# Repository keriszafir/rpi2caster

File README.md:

rpi2caster
==========

Raspberry Pi controls a Monotype composition caster.
----------------------------------------------------

Based on computer2caster by John Cornelisse Original idea described at
<http://letterpress.ch>

Typesetting and casting software for a Raspberry Pi-based computer
control attachment for Monotype composition casters.

This program suite consists of three major parts:

1.  Typesetting program for parsing UTF-8 text, calculating
    justification and coding it as a series of control codes accepted by
    the Monotype composition caster,
2.  Casting program for sending said codes to the casting machine using
    an interface with 32 pneumatic outputs, a pneumatic connection block
    attached to the caster's paper tower and a machine cycle
    sensor input. The program also allows to cast sorts, test the
    machine or set a short text on-the-fly, then cast the composed type.
3.  Inventory management program for adding, editing and deleting the
    definitions for replaceable machine components: normal wedges and
    matrix cases (diecases).

The workflow is as follows: 1. define matrix case layouts for your
matrix cases (and edit if needed), 2. define your normal wedges so that
the program knows what series in which set widths you have, 3. use a
typesetting program to generate a "ribbon" i.e. series of control codes
from a text, for a specified matrix case and normal wedge, 4. use the
casting program to test the machine/interface, perform machine
adjustments, and cast the type from ribbon you made earlier.

### Things you need to do

1.  Get a Raspberry Pi mod B+ or 2B and install Raspbian
2.  Use Raspbian jessie or stretch
3.  Make a pneumatic interface that attaches on the Monotype's paper
    tower - or have it made by someone with a CNC mill, 3D printer etc.
    This is the hardest part. The pneumatic interface must be very
    precisely done, so that no air leaks out.
4.  Get 31 three-way solenoid valves on valve islands. 12 or 24V DC.
    IMPORTANT: Some valves require minimum air pressure of 2...2.5bar.
    Since the Monotype caster uses 1bar, the pressure differential
    across the valve will be too low and the valve won't open. We need
    the 0bar minimum pressure variety, even though they may take more
    electrical power. A great candidate is the MATRIX BX758-8E1C3-24.
    The valve block is very compact and looks a bit like a
    stepper motor. It features up to 8 valves in a 55x55mm enclosure,
    with 12V DC or 24V DC controls and minimal pressure of 0 bar (this
    is important - we'll be using just 1bar!) The cost is about 200 Euro
    per piece (we need a set of 4). Another good candidates are e.g. two
    Festo CPV10-GE-MP-8 islands with 8 x "C" valve (i.e. dual 3/2) and
    separate connections for pilot supply.
5.  Make a RPi to 32 open collector output interface (the Raspberry's
    native GPIO pins cannot drive 24V loads, and there's not enough
    of them). Check out
    <https://github.com/elegantandrogyne/rpi2caster-doc-hardware> for
    the documentation (electrical in Eagle, PDF and Gerber, mechanical
    in CorelDraw) of my interface.
6.  Resolve the dependencies as described further.
7.  Install this software on your RPi.

### System config

The most common distro is Raspbian and we'll use jessie or newer. If you
need GUI (HDMI connection from Raspberry to monitor/TV, local console),
choose the standard image; otherwise (for headless setup) use minimal.
Assuming that you know your way around the Raspberry, SSH into it, set
it up (you must enable I2C), choose locale, change password, update the
system etc.

-   Network setup - I recommend configuring your router to offer the
    Raspberry a static DHCP lease based on the MAC address. If that's
    not possible (e.g. you don't have admin access to the router), use
    static IP address or scan the network for a host with the RPi's MAC
    address after each boot.
-   User & security config advice:
    1.  Create user accounts and disable no-password sudoing for "pi" by
        commenting out the respective line in /etc/sudoers.
    2.  Add new users to groups user "pi" belongs to. For security
        reasons, you may want to remove "pi" from the "sudo" and
        "adm" groups.
    3.  Since you'll log on the machine via SSH, you can use a RSA key
        authentication instead of entering a password on each logon.
        Either use a "ssh-copy-id \[target-username@\]target-host"
        command or create a \~/.ssh/authorized\_keys file on the
        Raspberry and paste your id\_rsa.pub contents there. Then you
        can just ssh by typing "ssh \[username@\]monotype" or via PuTTY.
-   Various improvements
    1.  You can enable GUI access by VNC. Install tightvncserver. Edit
        /etc/lightdm/lightdm.conf and uncomment the lines in
        VNC section. Change the port, geometry etc. if you wish. You
        don't have to create any init scripts; lightdm will already take
        care of running the VNC server. Just run "vncviewer \[hostname
        or IP addr\]:\[port\]" client-side and you'll get a lightdm
        login screen. Sign in to your account.
    2.  Using a web-based SSH client might be a good idea. I've used
        shellinabox with great results. This way, you won't have to
        install any additional software, esp. if you're using M\$
        Windows (otherwise, you'll need PuTTY or other SSH client).
-   Get rid of unneeded stuff! The original Raspbian distro has some
    unneeded software installed by default. We can get rid of it by
    using "sudo aptitude purge...":
    1.  wolfram-engine - removing it will clean somewhere around
        450MB (!)
    2.  X, LXDE etc. unless you want to VNC into the machine or set up a
        local console with GUI
    3.  anything related to Scratch
    4.  Minecraft or any other games, LibreOffice etc., they're huge
        diskspace hogs, not really needed

### Dependencies

Some of the dependencies will be marked as "(repo)". This means that you
can install them from Raspbian repository using apt or aptitude.

1.  python3 - doesn't come with minimal Jessie, and rpi2caster is
    written in python3 only (it's relatively new and there's no need for
    backwards compatibility)
2.  python3-pip - for installing python3 packages (install it with apt
    or aptitude; python3 will be installed automatically)
3.  wiringpi2-python - Python bindings for wiringpi2. You can install it
    with pip3: `sudo pip3 install wiringpi2` - necessary for program to
    work!

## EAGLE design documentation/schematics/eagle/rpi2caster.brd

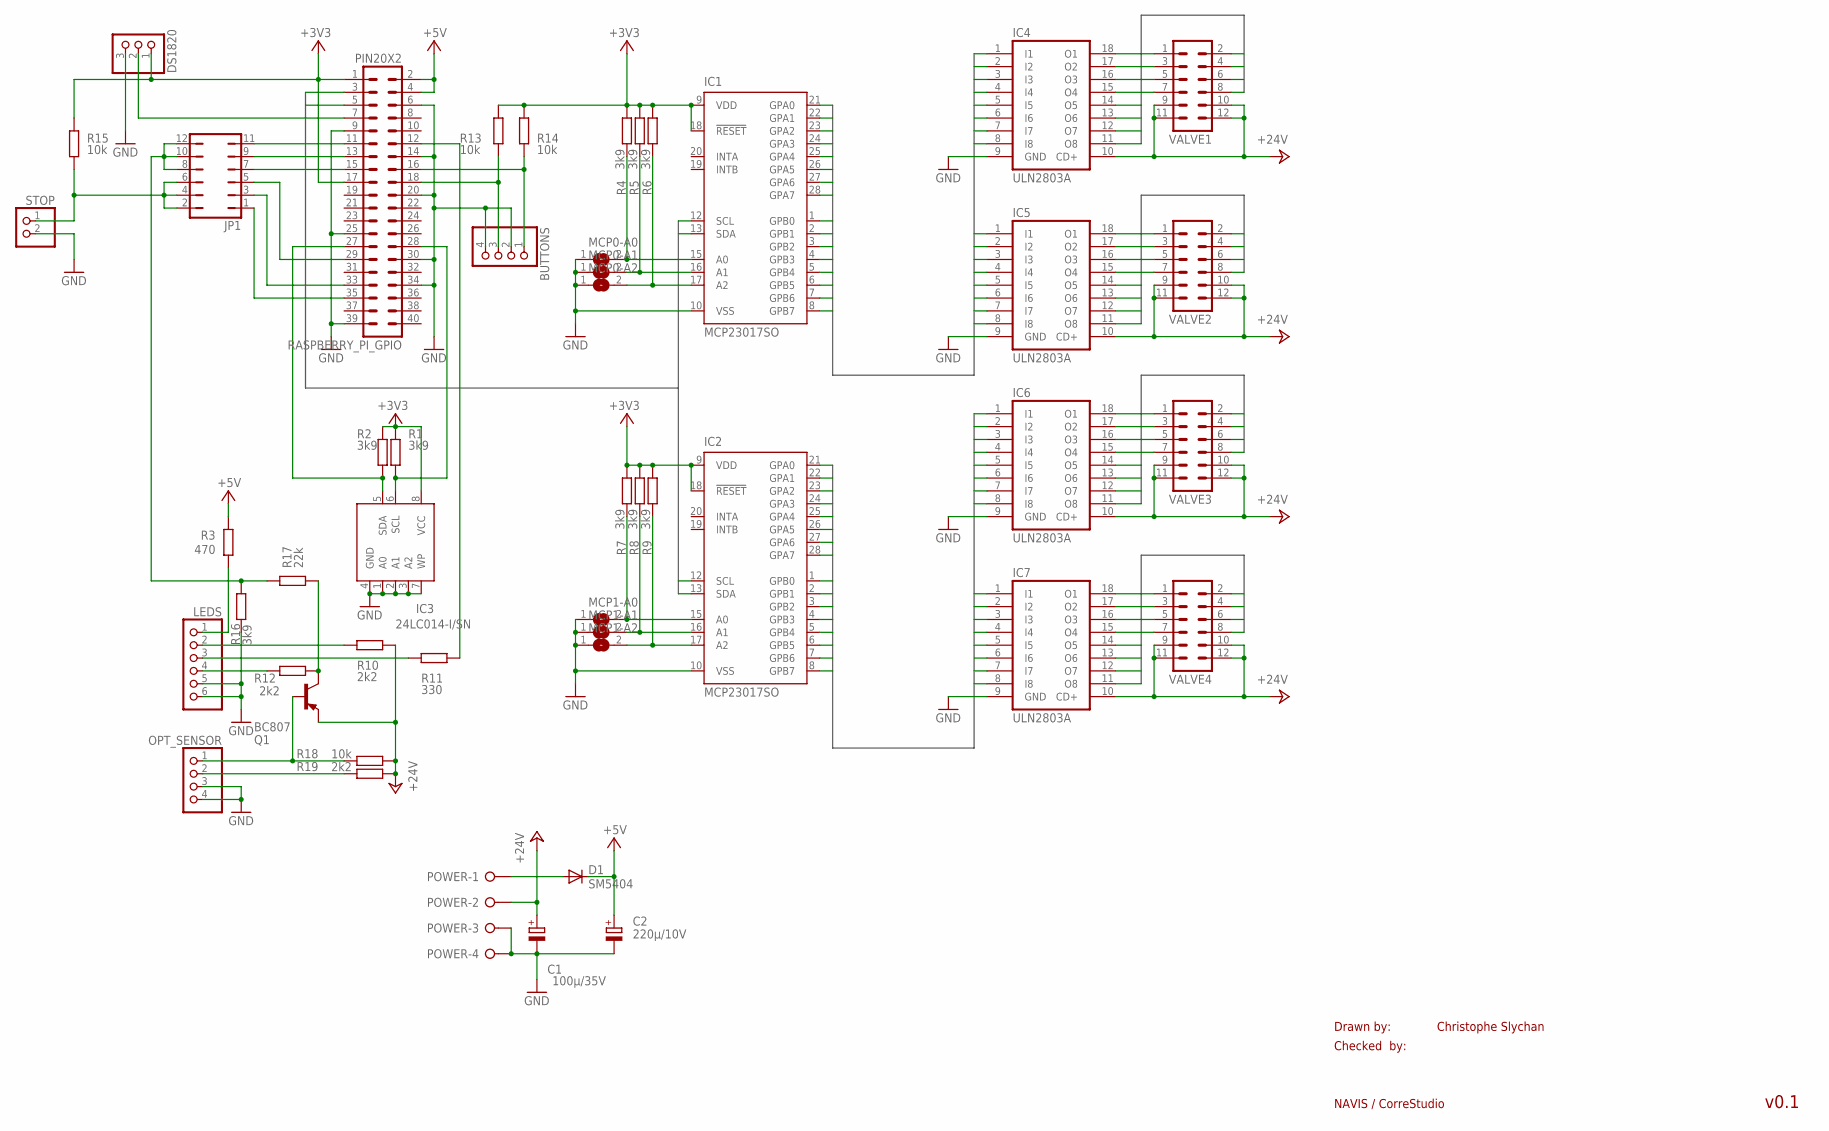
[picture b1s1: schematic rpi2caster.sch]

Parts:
BUTTONS: PINHD-1X4; 1X04
C1: 100µ/35V; E5-6
C2: 220µ/10V; E2,5-7
D1: SM5404; MELF-MLL41
DS1820: PINHD-1X3; 1X03
IC1, IC2: MCP23017SO; SO28W
IC3: 24LC014-I/SN; SOIC8
IC4, IC5, IC6, IC7: ULN2803A; SO18W
JP1: JP6Q
LEDS: PINHD-1X6; 1X06
MCP0-A0, MCP0-A1, MCP0-A2, MCP1-A0, MCP1-A1, MCP1-A2: SJ
OPT_SENSOR: PINHD-1X4; 1X04
POWER: W237-04P; W237-4P
Q1: BC807; SOT23-BEC
R1, R2, R4, R5, R6, R7, R8, R9, R16: 3k9; M0805; TOLERANCE 5%
R3: 470; M0805; TOLERANCE 5%
R10, R12, R19: 2k2; M0805; TOLERANCE 5%
R11: 330; M0805; TOLERANCE 5%
R13, R14, R15, R18: 10k; M0805; TOLERANCE 5%
R17: 22k; M0805; TOLERANCE 5%
RASPBERRY_PI_GPIO: PIN20X2; PIN_20X2
STOP: PINHD-1X2; 1X02
VALVE1, VALVE2, VALVE3, VALVE4: MA06-2

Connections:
+3V3: DS1820.1, IC1.9 (VDD), IC1.18 (!RESET), IC2.9 (VDD), IC2.18 (!RESET), IC3.8 (VCC), R1.1, R2.1, R4.2, R5.2, R6.2, R7.2, R8.2, R9.2, R13.2, R14.2, R15.2, RASPBERRY_PI_GPIO.1, RASPBERRY_PI_GPIO.17
+5V: C2.+, D1.C, R3.2, RASPBERRY_PI_GPIO.2, RASPBERRY_PI_GPIO.4
+24V: C1.+, IC4.10 (CD+), IC5.10 (CD+), IC6.10 (CD+), IC7.10 (CD+), POWER.2, Q1.E, R10.2, R18.1, R19.1, VALVE1.9, VALVE1.10, VALVE1.11, VALVE1.12, VALVE2.9, VALVE2.10, VALVE2.11, VALVE2.12, VALVE3.9, VALVE3.10, VALVE3.11, VALVE3.12, VALVE4.9, VALVE4.10, VALVE4.11, VALVE4.12
GND: BUTTONS.2, BUTTONS.4, C1.-, C2.-, DS1820.3, IC1.10 (VSS), IC2.10 (VSS), IC3.1 (A0), IC3.2 (A1), IC3.3 (A2), IC3.4 (GND), IC3.7 (WP), IC4.9 (GND), IC5.9 (GND), IC6.9 (GND), IC7.9 (GND), LEDS.5, LEDS.6, MCP0-A0.1, MCP0-A1.1, MCP0-A2.1, MCP1-A0.1, MCP1-A1.1, MCP1-A2.1, OPT_SENSOR.3, OPT_SENSOR.4, POWER.3, POWER.4, R16.1, RASPBERRY_PI_GPIO.6, RASPBERRY_PI_GPIO.9, RASPBERRY_PI_GPIO.14, RASPBERRY_PI_GPIO.20, RASPBERRY_PI_GPIO.25, RASPBERRY_PI_GPIO.30, RASPBERRY_PI_GPIO.34, RASPBERRY_PI_GPIO.39, STOP.2
I2C0: IC1.13 (SDA), IC2.13 (SDA), RASPBERRY_PI_GPIO.3
I2C1: IC1.12 (SCL), IC2.12 (SCL), RASPBERRY_PI_GPIO.5
MCP0_OUT0: IC1.21 (GPA0), IC4.8 (I8)
MCP0_OUT1: IC1.22 (GPA1), IC4.7 (I7)
MCP0_OUT2: IC1.23 (GPA2), IC4.6 (I6)
MCP0_OUT3: IC1.24 (GPA3), IC4.5 (I5)
MCP0_OUT4: IC1.25 (GPA4), IC4.4 (I4)
MCP0_OUT5: IC1.26 (GPA5), IC4.3 (I3)
MCP0_OUT6: IC1.27 (GPA6), IC4.2 (I2)
MCP0_OUT7: IC1.28 (GPA7), IC4.1 (I1)
MCP0_OUT8: IC1.1 (GPB0), IC5.8 (I8)
MCP0_OUT9: IC1.2 (GPB1), IC5.7 (I7)
MCP0_OUT10: IC1.3 (GPB2), IC5.6 (I6)
MCP0_OUT11: IC1.4 (GPB3), IC5.5 (I5)
MCP0_OUT12: IC1.5 (GPB4), IC5.4 (I4)
MCP0_OUT13: IC1.6 (GPB5), IC5.3 (I3)
MCP0_OUT14: IC1.7 (GPB6), IC5.2 (I2)
MCP0_OUT15: IC1.8 (GPB7), IC5.1 (I1)
MCP1_OUT0: IC2.21 (GPA0), IC6.8 (I8)
MCP1_OUT1: IC2.22 (GPA1), IC6.7 (I7)
MCP1_OUT2: IC2.23 (GPA2), IC6.6 (I6)
MCP1_OUT3: IC2.24 (GPA3), IC6.5 (I5)
MCP1_OUT4: IC2.25 (GPA4), IC6.4 (I4)
MCP1_OUT5: IC2.26 (GPA5), IC6.3 (I3)
MCP1_OUT6: IC2.27 (GPA6), IC6.2 (I2)
MCP1_OUT7: IC2.28 (GPA7), IC6.1 (I1)
MCP1_OUT8: IC2.1 (GPB0), IC7.8 (I8)
MCP1_OUT9: IC2.2 (GPB1), IC7.7 (I7)
MCP1_OUT10: IC2.3 (GPB2), IC7.6 (I6)
MCP1_OUT11: IC2.4 (GPB3), IC7.5 (I5)
MCP1_OUT12: IC2.5 (GPB4), IC7.4 (I4)
MCP1_OUT13: IC2.6 (GPB5), IC7.3 (I3)
MCP1_OUT14: IC2.7 (GPB6), IC7.2 (I2)
MCP1_OUT15: IC2.8 (GPB7), IC7.1 (I1)
unnamed: LEDS.1, R3.1
unnamed: IC3.5 (SDA), R2.2, RASPBERRY_PI_GPIO.27
unnamed: IC3.6 (SCL), R1.2, RASPBERRY_PI_GPIO.28
unnamed: OPT_SENSOR.2, R19.2
unnamed: DS1820.2, RASPBERRY_PI_GPIO.7
unnamed: IC1.15 (A0), MCP0-A0.2, R4.1
unnamed: IC1.16 (A1), MCP0-A1.2, R5.1
unnamed: IC1.17 (A2), MCP0-A2.2, R6.1
unnamed: IC2.15 (A0), MCP1-A0.2, R7.1
unnamed: IC2.16 (A1), MCP1-A1.2, R8.1
unnamed: IC2.17 (A2), MCP1-A2.2, R9.1
unnamed: LEDS.2, R10.1
unnamed: LEDS.3, R11.1
unnamed: LEDS.4, R12.1
unnamed: JP1.11, RASPBERRY_PI_GPIO.11
unnamed: JP1.9, RASPBERRY_PI_GPIO.13
unnamed: R11.2, RASPBERRY_PI_GPIO.12
unnamed: BUTTONS.1, R14.1, RASPBERRY_PI_GPIO.16
unnamed: BUTTONS.3, R13.1, RASPBERRY_PI_GPIO.18
unnamed: JP1.2, JP1.4, JP1.6, R15.1, STOP.1
unnamed: JP1.8, JP1.10, JP1.12, R16.2, R17.2
unnamed: OPT_SENSOR.1, Q1.B, R18.2
unnamed: Q1.C, R12.2, R17.1
unnamed: JP1.7, RASPBERRY_PI_GPIO.15
unnamed: JP1.5, RASPBERRY_PI_GPIO.29
unnamed: JP1.3, RASPBERRY_PI_GPIO.33
unnamed: JP1.1, RASPBERRY_PI_GPIO.35
unnamed: D1.A, POWER.1
VALVE1_1: IC4.11 (O8), VALVE1.1
VALVE1_2: IC4.12 (O7), VALVE1.2
VALVE1_3: IC4.13 (O6), VALVE1.3
VALVE1_4: IC4.14 (O5), VALVE1.4
VALVE1_5: IC4.15 (O4), VALVE1.5
VALVE1_6: IC4.16 (O3), VALVE1.6
VALVE1_7: IC4.17 (O2), VALVE1.7
VALVE1_8: IC4.18 (O1), VALVE1.8
VALVE2_1: IC5.18 (O1), VALVE2.1
VALVE2_2: IC5.17 (O2), VALVE2.2
VALVE2_3: IC5.16 (O3), VALVE2.3
VALVE2_4: IC5.15 (O4), VALVE2.4
VALVE2_5: IC5.14 (O5), VALVE2.5
VALVE2_6: IC5.13 (O6), VALVE2.6
VALVE2_7: IC5.12 (O7), VALVE2.7
VALVE2_8: IC5.11 (O8), VALVE2.8
VALVE3_1: IC6.18 (O1), VALVE3.1
VALVE3_2: IC6.17 (O2), VALVE3.2
VALVE3_3: IC6.16 (O3), VALVE3.3
VALVE3_4: IC6.15 (O4), VALVE3.4
VALVE3_5: IC6.14 (O5), VALVE3.5
VALVE3_6: IC6.13 (O6), VALVE3.6
VALVE3_7: IC6.12 (O7), VALVE3.7
VALVE3_8: IC6.11 (O8), VALVE3.8
VALVE4_1: IC7.11 (O8), VALVE4.1
VALVE4_2: IC7.12 (O7), VALVE4.2
VALVE4_3: IC7.13 (O6), VALVE4.3
VALVE4_4: IC7.14 (O5), VALVE4.4
VALVE4_5: IC7.15 (O4), VALVE4.5
VALVE4_6: IC7.16 (O3), VALVE4.6
VALVE4_7: IC7.17 (O2), VALVE4.7
VALVE4_8: IC7.18 (O1), VALVE4.8

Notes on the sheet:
Drawn by:
Checked by:
NAVIS / CorreStudio
Christophe Slychan
v0.1

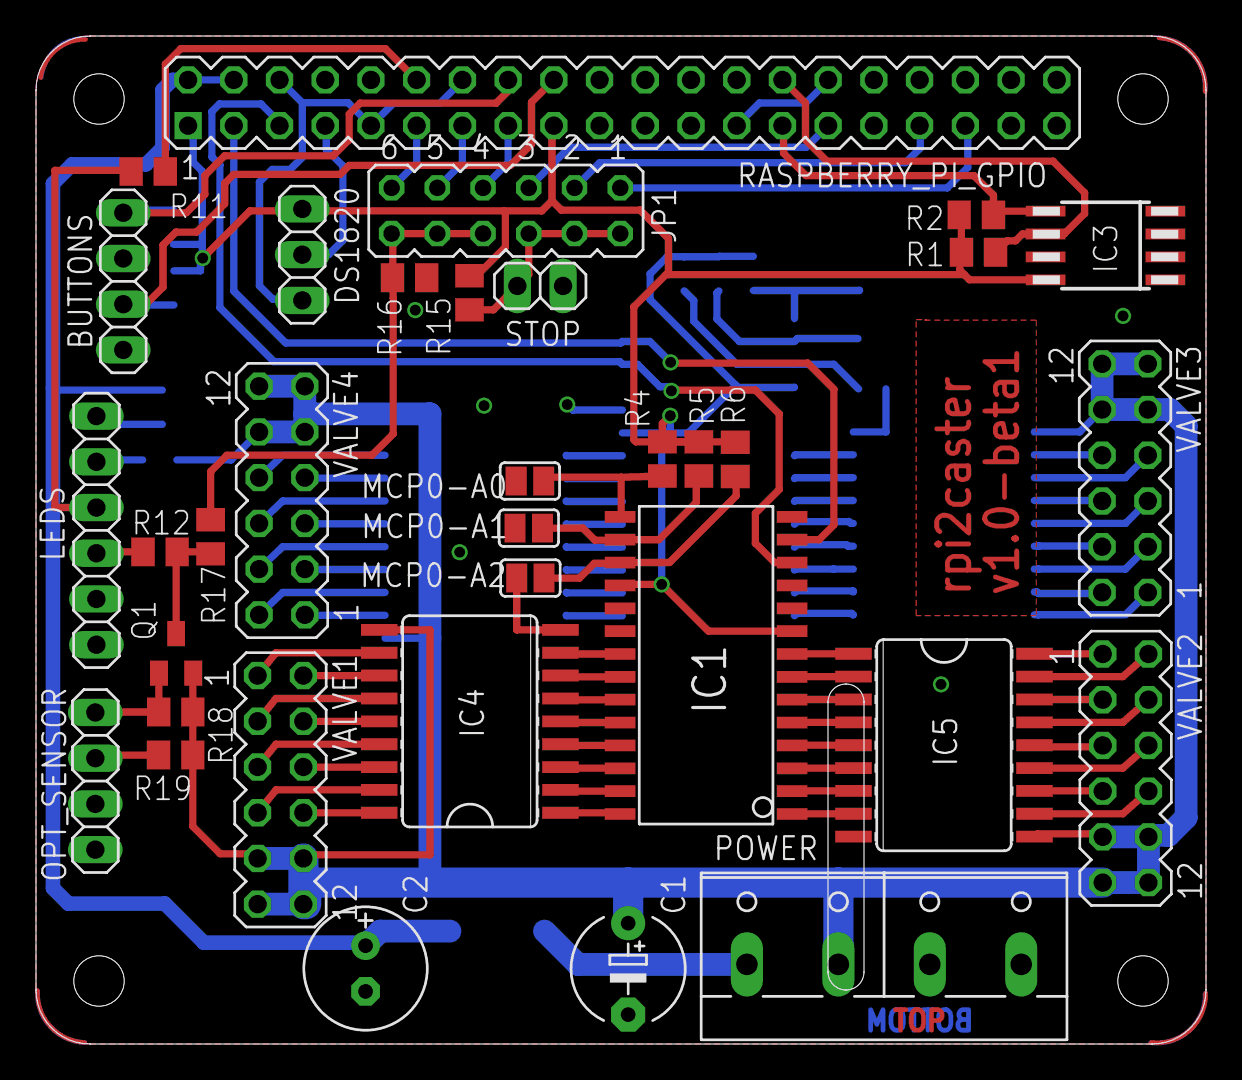
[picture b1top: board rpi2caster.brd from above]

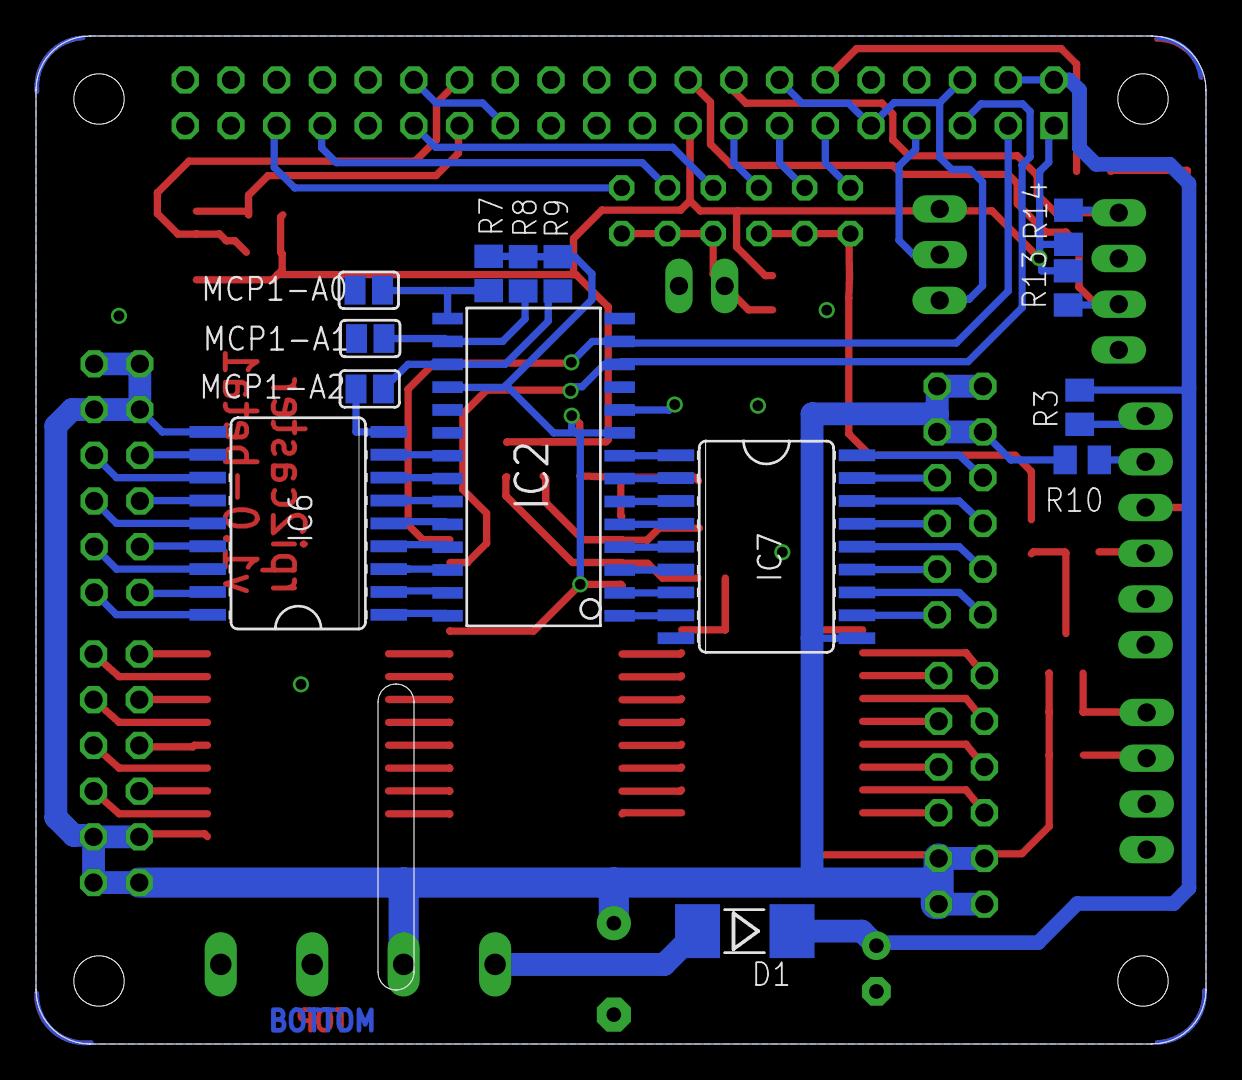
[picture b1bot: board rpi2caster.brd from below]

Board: 2 copper layers, 65.0 x 56.0 mm, 48 parts (14 on the bottom side), 98 nets.

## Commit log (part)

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2016-02-15 Ship the fix to PyPI
2016-02-15 Start integrating workflows in casting and perforation...
2016-02-16 Configuration parsing bugfix
2016-02-17 Modular casting rework in progress
2016-02-17 Sorts casting debug
2016-02-18 Work on casting function
2016-02-18 Fix temporary ribbon setting being not so temporary after all...
2016-02-18 More work on stats... and ribbon relations as well
2016-02-18 Better ribbon, diecase, wedge and stats updating, using property decorators
2016-02-19 Pump status update and restart logic rework in progress
2016-02-19 Debug wrong configuration
2016-02-19 Bugfix: hardware instantiation where unneeded
2016-02-19 Sensor and output release (instance deletion) before casting
2016-02-19 Add a hack for not reusing pin numbers with wiringPi
2016-02-19 Fix import loop
2016-02-19 Fix prompt in ui.confirm
2016-02-19 Rework of menu system; add direct casting mode with no menu; various bugfixes
2016-02-20 Various fixes and reworks
2016-02-21 Simplify the wedge, diecase, ribbon and work choice workflow
2016-02-22 Various fixes and refactors
2016-02-22 Work on statistics getting and setting
2016-02-22 Linting and regression fixes
2016-02-23 Add line skipping in casting mode
2016-02-24 More stat tweaks
2016-02-25 Space and sorts casting; diecase calibration; various fixes and reworks
2016-02-26 Support for HMN and unit-shift during casting
2016-02-26 Add comments in space casting
2016-02-27 Ditch the unit shift; ditch the works; add fount schemes instead (in ORM layer for now)
2016-02-27 Add metadata when exporting ribbon files
2016-02-27 Move processing O15 and row 16 to a decorator over casting.process
2016-03-01 Rewrite and refactor the stats logic - still on the hunt for some bugs
2016-03-02 Refactor stats.code_parameters, fix bug in monotype.adjust_signals that would turn all on in testing mode
2016-03-02 Further tweaking, testing and debugging in stats section
2016-03-02 Push to PyPI
2016-03-02 Casting workflow fixes
2016-03-04 Matrix auto-selection for casting typecases and typesetting; minor reworks on casting workflow; work on typesetting program
2016-03-06 Further work on diecase layout editing
2016-03-07 Better line length setting
2016-03-07 Casting sorts with no diecase selected: char and style(s) no longer needed
2016-03-08 Change casting sorts, add draw rod calibration
2016-03-08 Disable the ad-hoc typesetting - undergoing rework
2016-03-09 Work on typecase casting functions
2016-03-10 Add hundreds of new wedge definitions
2016-03-12 Rework of ribbon model
2016-03-13 Add diecase and wedge selection by command line parameter; rework wedge choice - display old style names, parse new style names only (KISS!)
2016-03-14 More usability fixes
2016-03-14 More powerful matrix lookup in diecase
2016-03-14 Simplify edit matrix, rearrange Matrix class to put attributes at the end
2016-03-15 Rework of sorts casting; usability fixes for diagnostics - default repeat
2016-03-15 Better batch casting - fill lines to desired length;
2016-03-16 Cast sorts/spaces/typecases rework to build upon cast_batch; UI input prompts rework; raise ReturnToMenu on blank filenames
2016-03-16 Simplify casting - no more lines of quads and preheat mould. This will be specified upstream.
2016-03-16 Fix for space styles in matrix case layout editor
2016-03-16 Bugfix in diecase selection
2016-03-16 Mould prehead quad quantity fix
2016-03-17 Optimize the generators in ribbon parser in stats module; work on new typecase casting based on letter frequencies
2016-03-18 Further menu tweaks
2016-03-18 Remove mention of deprecated inventory management mode
2016-03-19 Remove unneeded defaults; set wedge parser-wise Add matrix units re-calculation for alternative wedge
2016-03-20 Alternative wedge getter bugfix
2016-03-26 Class-based language selection and typecase casting
2016-03-26 Disable line skipping for 1-line cast jobs
2016-03-26 Space casting: move to point calculations and refactor
2016-03-26 Minor fixes
2016-03-26 Do not display units on manual matrix choice if multiple matches
2016-03-26 Move text_ui.enter_line_length to typesetting_funcs.enter_measure; change output to points; refactor ts_f a bit
2016-03-26 Add unit values for S791 wedge
2016-03-26 Boost point calculation precision; make wedge_positions an attribute
2016-03-26 Minor fix in enter_measure parameter
2016-03-27 Style and width limits fix for spaces
2016-03-27 Move to string-based coordinate setting for Matrix objects
2016-03-27 Data model change (BREAKS COMPATIBILITY): diecase layout: styles -> string; column string, row int -> coordinates string
2016-04-01 Rebuild of matrix backend; work on galley building; performance testing and debugging; typecase casting functionality
2016-04-01 Mode cleanup on exception
2016-04-03 Use explicit "from module import Class"; refactor styles
2016-04-03 Line class for typesetting
2016-04-03 Casting workflow refactor, fixes in diagnostics routines
2016-04-03 Readability tweaks
2016-04-03 Add testing function for HMN, KMN and unit-shift
2016-04-03 Start new typesetting utility
2016-04-05 Typesetting session
2016-05-01 Vast remodelling; user-based configuration and database; length class etc.
2016-05-01 Final touches before release
2016-05-03 Bugfix in mat boolean and galley builder
2016-05-05 Bump version
2016-05-07 Add backend for old parallel interface from Symbiosys; minor changes follow; rework singleton
2016-05-07 UI tweaks
2016-05-07 Matrix editor tweaks
2016-05-08 Minor display tweaks
2016-05-08 Matrix swapping
2016-05-09 WiringPi output driver regression fix
2016-05-09 Mode resetting bugfix
2016-05-09 Rework of the configuration backend
2016-05-09 Update default conffile, tweak diecase layout
2016-05-09 Empty ribbon choice crash fix
2016-05-09 Sensor override fix for parallel interface
2016-05-09 New and improved casting backend choice mechanism
2016-05-09 Parallel driver now has a configurable signals arrangement
2016-05-14 Caster backend setting bugfix and refactoring
2016-05-31 Typesetting work in progress
2016-05-31 Alternative wedge selection refactor
2016-06-01 Ask about wedge and measure just-in-time; remove select wedge/measure features
2016-06-08 Space casting rework; diecase proofing; unit arrangement functionality; new Space class for spaces
2016-06-09 Space getting mechanism for diecases
    fix typo
2016-06-10 driver fixes; change debounce time to 100ms
2016-06-10 Bugfix: wrong object attribute
2016-06-11 Bugfix in unit arrangement get_unit_value
2016-06-13 Matrix case editing and completeness checking fixes
2016-06-14 Minor refactors and code readability improvements
2016-06-14 Fix missing comma
2016-06-14 Blow all tweaks
2016-06-14 Transfer wedge calibration fix
2016-06-20 Minor bugfix
2016-06-23 Safeguard against negative value runs adding
2016-07-01 Configurable GPIOs to work with gpiodaemon
2016-07-04 Rework of casting/statistics engine
2016-07-08 First batc of bugfixes
2016-07-11 Enable using RPi.GPIO sensor
2016-07-11 Make RPi.GPIO sensor available by default
2016-07-11 Bump bouncetime to 50ms
2016-07-11 Make the sysfs sensor a singleton
2016-07-11 Debugging further...
2016-07-12 Punching by default for "punching" sensor in conffile
2016-07-12 Fix some bugs in mode properties
2016-07-12 Testing and debugging mode setting
2016-07-13 Change sensor/output setting and resetting
2016-07-13 Set the modes at the beginning
2016-10-30 Rework of database/configuration engine, in progress... Add mysql and postgres backends
2017-02-08 Reworks on main program, diecase charset, typesetting, etc.
2017-02-08 finish refactoring: try/except(pass)->contextlib.ignored
2017-02-09 Rework of attribute setting, session initialization etc. WARNING: needs more QA
2017-02-09 factor out complications in main module and fix ribbon manual choice
2017-03-12 Remodel the diecase layout backend
2017-03-23 Testing and debugging - row 16 addressing mode, ui.simple_menu...
2017-04-15 Rework of architecture. Breaks compatibility.
2017-04-19 Further casting utility modification, rework of data resources, add unit arrangement definitions for a ton of UAs, add support for getting UA for a diecase
2017-04-26 some bugfixes
2017-04-28 implement typeface name listing; new language/text completeness checking
2017-05-08 Add QR code generation and casting; rework handsetting material sequence generation
2017-05-09 improved wedge position calculation and unit limiting
2017-05-09 remake diecase proof casting
2017-05-20 fix wrong call in case of selecting simulation
2017-05-20 Bugfixes for casting
2017-05-21 refactors and bugfixes in casting stats; rework of failed casting behaviour
2017-05-22 debugging smbus output sequence
2017-05-22 debugging smbus output sequence - finished
2017-05-22 fix casting stats not resetting properly between jobs
2017-05-24 better line fill behaviour on material casting
2017-05-24 workaround for being unable to match a space [2]
2017-05-26 moved to peewee as ORM
2017-05-26 rearrange __init__.py - to match sequence of imports
2017-05-26 __init__ rework
2017-05-29 move from argparse to click; resolve runtime config at the top level; redesign interface instantiation
2017-05-29 changes in simulation mode setting
2017-06-02 rebuild the main menu and argument parsing - in progress...
2017-06-02 refactor the inventory editor menu
2017-06-03 simplify configuration
2017-06-04 minor tweaks; remove unused code
2017-06-04 add diecase layout resizing to the editor
2017-06-04 remake diecase layout legend
2017-06-26 moving to the new client-server hardware controller...
2017-07-04 fully redesign the caster interaction
2017-07-05 add variety in user output for simulation casting
2017-07-06 rename testing -> testing_mode
2017-07-06 add machine switchover
2017-07-06 handle error in case of wrong filename
2017-07-06 try to autodetect the version
2017-07-06 add an exception handler for non-JSON responses
2017-07-08 interface selection menu tweaks
2017-07-09 testing mode fixes
2017-07-12 bugfix in casting
2017-07-13 menu fixes
2017-07-13 prepare to release
2017-07-13 now automatically create tables if OperationalError is caught when selecting data
2017-07-14 UI enhancements
2017-07-14 further UI fixes; rework diecase/mould blade calibration to work witout diecase
2017-07-14 diecase layout display fix
2017-07-14 pushing to PyPI
2017-07-24 Casting process fixes, UI enhancements, typeface/UA metadata support, diecase edition changes, style collection masking, style chooser, typeface data for 262+275 and 327+334, various other refactors
2017-07-26 add support for alternative italic and semi-bold; refactor styles
2017-07-26 fix pump not going on in calibration
2017-07-27 change sequence of diecase/bridge adjustment
2017-07-29 add customizable typeface/unit arrangement/wedge definition/letter frequencies data
2017-07-29 caster choice fix
2017-07-29 Bugfix in caster name
2017-07-30 factor out the layout size attribute; use class inheritance now
2017-07-30 refactor diecase-layout relationship to use inheritance rather than attribute; needs testing
2017-08-01 Diecase caching bugfix prevents instantiating new diecases if empty is currently used; remodel diecase proof; re-enable layout editing on empty diecases
2017-08-06 rework typeface sizes, add views for diecase metadata, typeface, UA and wedge, fix some bugs, work on typesetting utility
2017-08-07 parsing document into paragraphs (plus some definition changes)
2017-12-13 different start/stop sequences depending on the interface has_motor_control capabliity
2018-06-08 END OF LINE, fixes for demonstration...
2018-06-08 working on release for JC
2018-06-08 fix version
2018-06-08 maybe this time... [PyPI fix]
2018-06-08 add confirmation prompts for sorts
2018-11-30 New release with massive code changes
2018-11-30 remove unused module
2018-12-01 modifications and refactors
2018-12-04 add casting from Excel files; separate chunks of type with quads in cast_material and cast_xls; various fixes
2018-12-05 changes in casting.read_xls, functions.make_galley and monotype.MonotypeCaster (handle MachineStopped in start() and stop()
2018-12-06 fixes in simulation casting; correct signal parsing and wedge position reporting
2018-12-10 add start after emergency stop in punching mode
2018-12-12 main menu / arguments rework
2018-12-14 remodel command line arguments; get rid of Casting class, move to functions instead
2018-12-14 use cast_galley as a separate function for preparing ribbons from mat queues
2018-12-18 fix timeouts
